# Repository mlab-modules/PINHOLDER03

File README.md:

# PINHOLDER03A

Single PIN diode holder for PCRD01A

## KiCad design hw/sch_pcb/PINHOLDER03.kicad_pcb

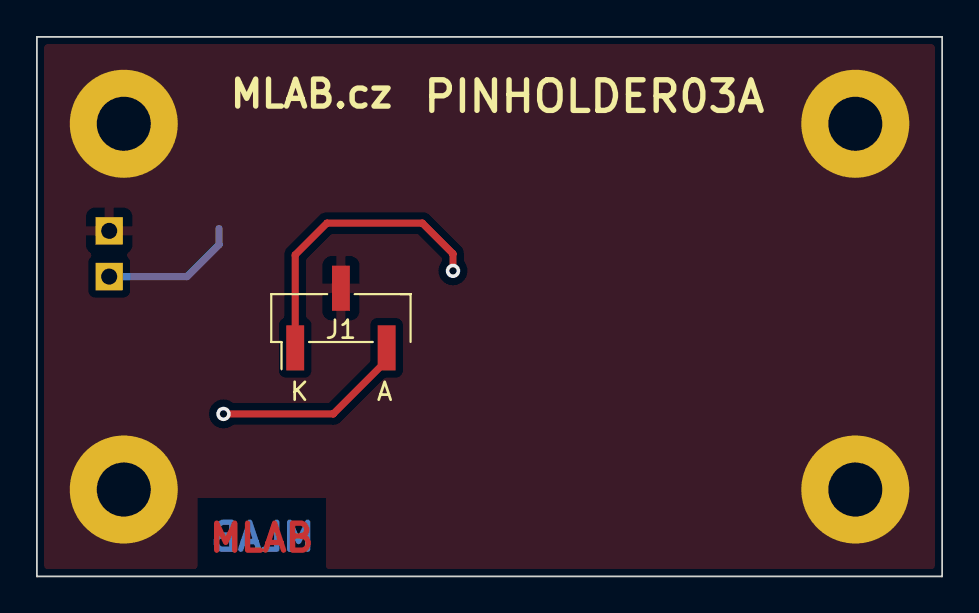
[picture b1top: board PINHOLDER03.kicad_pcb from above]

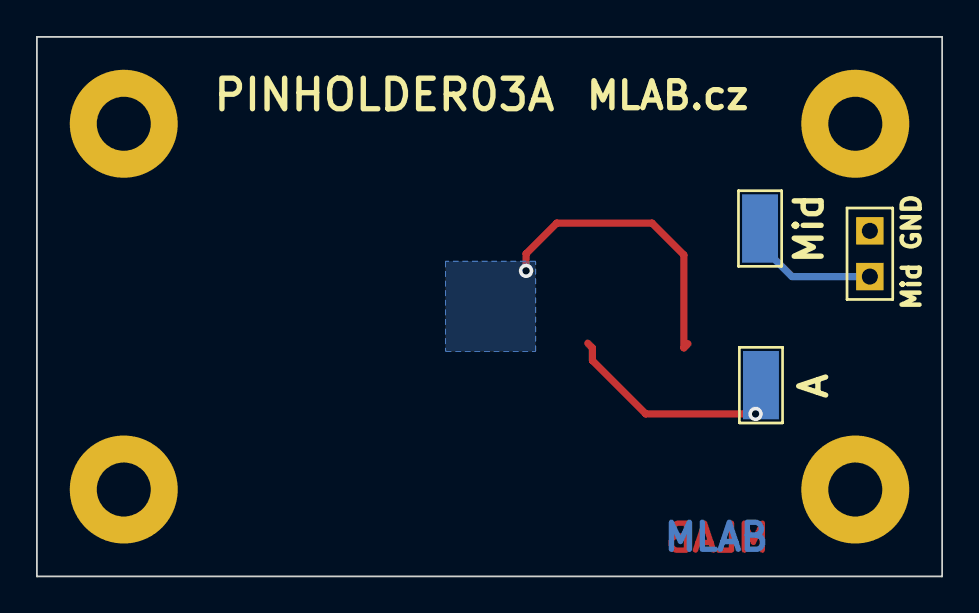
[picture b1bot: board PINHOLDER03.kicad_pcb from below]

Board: 2 copper layers, 50.3 x 30.0 mm, 9 parts (4 on the bottom side), 4 nets.

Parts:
J1: HEADER_1x03; PinHeader_1x03_P2.54mm_Vertical_SMD_Pin1Left
J2: HEADER_1x02; Straight_1x02
M1, M2, M3, M4: HOLE; MountingHole_3mm
TP1: TestPoint; TestPoint_Pad_D0.5mm_noSilk
TP2, TP4: TestPoint; TestPoint_Keystone_5019_Minature

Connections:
/circle_0: J1.1, TP1.1
GND: J1.2, J2.1, M1.1, M2.1, M3.1, M4.1
unnamed: J2.2, TP4.1
unnamed: J1.3, TP2.1

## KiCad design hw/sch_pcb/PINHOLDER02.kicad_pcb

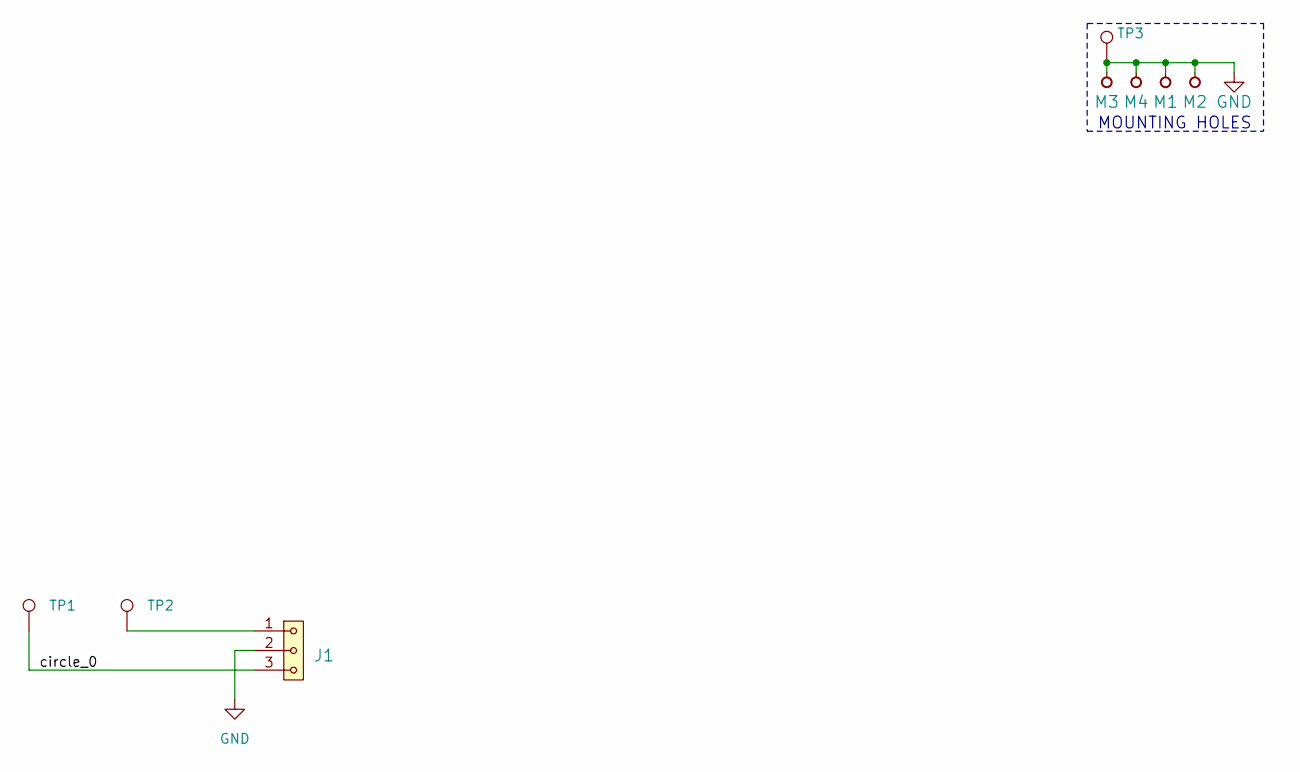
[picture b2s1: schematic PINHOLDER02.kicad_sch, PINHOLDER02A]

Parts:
J1: HEADER_1x03; PinHeader_1x03_P2.54mm_Vertical_SMD_Pin1Left
M1, M2, M3, M4: HOLE; MountingHole_3mm
TP1, TP2, TP3: TestPoint; TestPoint_Pad_D0.5mm_noSilk

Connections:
/circle_0: J1.3, TP1.1
GND: J1.2, M1.1, M2.1, M3.1, M4.1, TP3.1
unnamed: J1.1, TP2.1

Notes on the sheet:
MOUNTING HOLES

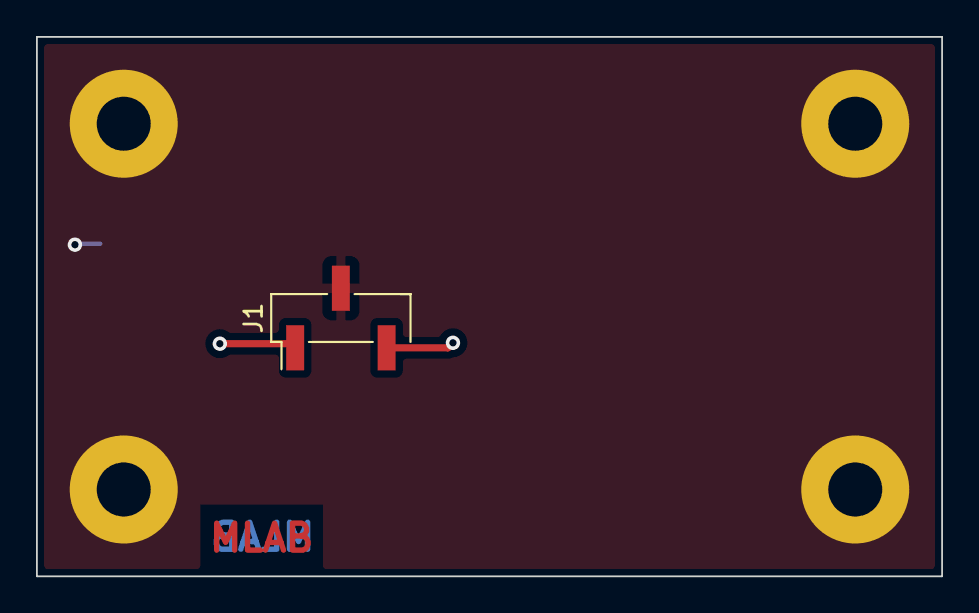
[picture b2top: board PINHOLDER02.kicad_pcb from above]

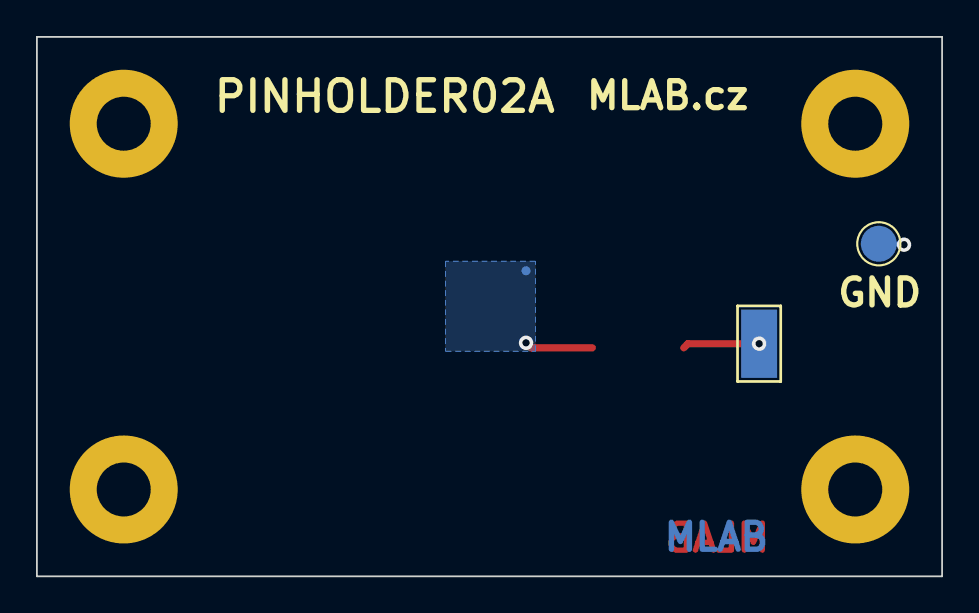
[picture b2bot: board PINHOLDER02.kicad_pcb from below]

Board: 2 copper layers, 50.3 x 30.0 mm, 8 parts (3 on the bottom side), 3 nets.

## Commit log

2023-04-10 Update metadata files
2023-04-10 change submodule
2023-04-11 intial version
2023-04-12 uprava layoutu
2023-04-12 update gitmodules
2023-04-12 Update actions products
2023-04-12 uprava layoutu pro PCRD01A
2023-04-12 uprava layoutu, 2 diody
2023-04-12 Fix typo in the name. Cleanup layout.
2023-04-13 zamena anoda-katoda diody
2023-04-13 text ve schematu
2023-04-13 cleanup repository and copy of name to F silkscreen.
2023-04-13 Make shape ortogonal.
2023-04-13 Update workflow files
2023-04-13 Set specific units for dimensions.
2023-04-13 Edit PCB
2023-04-13 subomudel
2023-04-13 assets
2023-05-25 automated commit; add github actions
2023-07-05 automated commit; rename source files to new naming convence
2023-09-16 Update image to image_title
2023-09-16 Update status
